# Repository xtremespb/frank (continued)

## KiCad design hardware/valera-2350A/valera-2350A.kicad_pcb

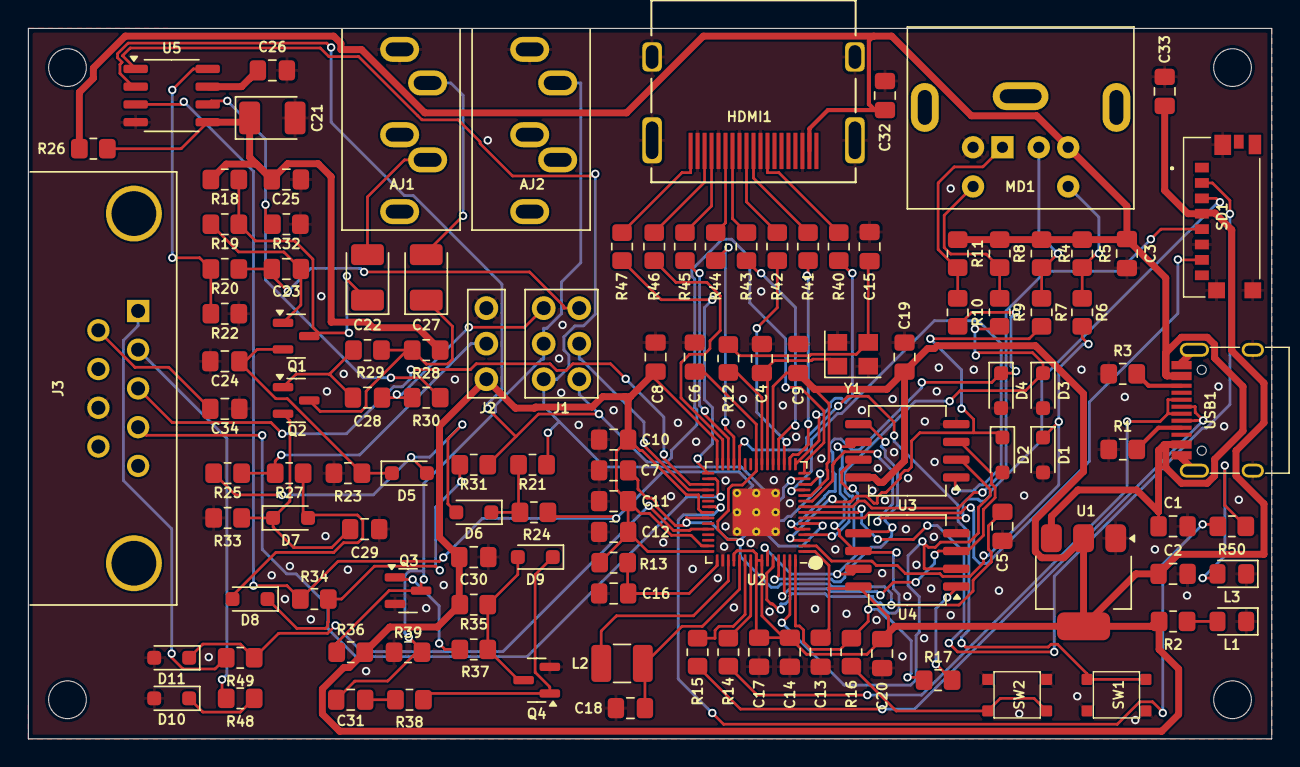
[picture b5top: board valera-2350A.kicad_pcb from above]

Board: 2 copper layers, 88.9 x 50.8 mm, 123 parts (0 on the bottom side), 92 nets.

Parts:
AJ1: Audio OUT; Jack (3.5mm)
AJ2: Audio In; Jack (3.5mm)
C1, C2, C3: 10u; Capacitor (0805)
C4, C15: 15p; Capacitor (0805)
C5, C7, C8, C9, C10, C11, C12, C13, C14, C19, C20, C24, C25, C29, C30, C31, C32, C33, C34: 100n; Capacitor (0805)
C6, C16, C17, C18: 4.7u; Capacitor (0805)
C21, C22, C27: 10u; Capacitor (3528, tantalum, polar)
C23, C26, C28: 1u; Capacitor (0805)
D1, D2, D3, D4, D10, D11: 3V3; Diode (SOD-323)
D5, D6, D7, D8, D9: 1N4148; Diode (SOD-323)
H1, H2, H3, H4: MountingHole; Mounting Hole (2.7mm)
HDMI1: HDMI Female; HDMI (female)
J1: Audio Jumpers; Pin Header (2x03)
J2: PWM Jumper; Pin Header (1x03)
J3: Gamepad; D-SUB (9 pin, male, top mount)
L1: Green; LED (0805)
L2: 3.3u; Inductor (3225)
L3: Blue; LED (0805)
MD1: Mini-DIN-6; MiniDIN (6 Pin, female)
Q1, Q2, Q3, Q4: BC850; SOT-23
R1, R3: 5.1K; Resistor (0805)
R2, R4, R5, R8, R12, R16, R18, R22, R28, R32, R36, R48, R49, R50: 1K; Resistor (0805)
R6, R7, R9, R10, R23, R39: 100R; Resistor (0805)
R11: 1k; Resistor (0805)
R13: 33R; Resistor (0805)
R14, R15: 27R; Resistor (0805)
R17: 0R; Resistor (0805)
R19, R29: 100K; Resistor (0805)
R20, R30: 20K; Resistor (0805)
R21, R31: 51R; Resistor (0805)
R24, R25, R27, R34: 200R; Resistor (0805)
R26: 10R; Resistor (0805)
R33: 100; Resistor (0805)
R35, R37, R38: 10K; Resistor (0805)
R40, R41, R42, R43, R44, R45, R46, R47: 270R; Resistor (0805)
SD1: 47571-0001; MicroSD (SMD, short)
SW1: Reset; Button (SMD, 3x3mm, 1-1)
SW2: Boot; Button (SMD, 3x3mm, 1-1)
U1: NCP1117 3.3; SOT-223
U2: RP2350A; QFN 60 (RP2350A)
U3: ESP-PSRAM32; SOIC-8
U4: W25Q128JVSQ; SOIC-8
U5: TDA1387T; SO-8
USB1: USB Type C
Y1: ABM8-272-T3; Crystal (3225)

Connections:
+3V3: C2.1, C8.1, C9.1, C10.1, C11.1, C12.1, C13.1, C14.1, C17.1, C19.1, C20.1, C30.1, C33.2, J2.3, R2.2, R13.1, R35.1, R36.1, SD1.P4 (VDD), U1.2 (VO), U2.1 (IOVDD), U2.11 (IOVDD), U2.20 (IOVDD), U2.30 (IOVDD), U2.38 (IOVDD), U2.44 (ADC_AVDD), U2.45 (IOVDD), U2.49 (VREG_VIN), U2.53 (USB_OTP_VDD), U2.54 (QSPI_IOVDD), U3.8 (VCC), U4.8 (VCC)
/Audio Out/+5VA: C21.1, C25.1, R18.1, R26.1, R28.1, U5.5 (VA)
/Audio Out/L: AJ1.T, C27.2
/Audio Out/R: AJ1.R, C22.2
/D+: R14.1, USB1.6 (DP1), USB1.8 (DP2)
/D-: R15.1, USB1.5 (DN2), USB1.7 (DN1)
/GPIO0: D1.1 (K), R6.2, U2.2 (GPIO0)
/GPIO1: D2.1 (K), R7.2, U2.3 (GPIO1)
/GPIO2: D3.1 (K), R9.2, U2.4 (GPIO2)
/GPIO3: D4.1 (K), R10.2, U2.5 (GPIO3)
/GPIO4: SD1.P7 (DAT0), U2.7 (GPIO4)
/GPIO5: SD1.P2 (CD/DAT3), U2.8 (GPIO5)
/GPIO6: SD1.P5 (CLK), U2.9 (GPIO6)
/GPIO7: SD1.P3 (CMD), U2.10 (GPIO7)
/GPIO8: U2.12 (GPIO8), U3.1 (~CE)
/GPIO9: R24.2, R34.2, U2.13 (GPIO9), U5.3 (DATA)
/GPIO10: J1.5, R21.2, U2.14 (GPIO10), U5.1 (SCLK)
/GPIO11: J1.6, R31.2, U2.15 (GPIO11), U5.2 (LRCK)
/GPIO12: R40.2, U2.16 (GPIO12)
/GPIO13: R41.2, U2.17 (GPIO13)
/GPIO14: R42.2, U2.18 (GPIO14)
/GPIO15: R43.2, U2.19 (GPIO15)
/GPIO16: R44.2, U2.27 (GPIO16)
/GPIO17: R45.2, U2.28 (GPIO17)
/GPIO18: R46.2, U2.29 (GPIO18)
/GPIO19: R47.2, U2.31 (GPIO19)
/GPIO20: J3.4, U2.32 (GPIO20)
/GPIO21: J3.3, U2.33 (GPIO21)
/GPIO22: J1.4, U2.34 (GPIO22)
/GPIO26: D10.1 (K), R48.1
/GPIO27: D11.1 (K), R49.1, U2.41 (GPIO27_ADC1)
/Gamepad/+5V: C34.1, J3.6
/Gamepad/J1_DATA: J3.2, R48.2
/Gamepad/J2_DATA: J3.1, R49.2
/LEFT_OUT: C28.1, J1.1, R30.2
/LOAD_IN_D: AJ2.T, C31.1, J1.3, Q3.3 (C), R36.2, R39.1
/PS2/PS/2 CLK: MD1.5, R8.2, R9.1
/PS2/PS/2 DATA: MD1.1, R10.1, R11.2
/PWM_EN: J2.2, R25.2, R27.1
/RIGHT_OUT: C23.1, J1.2, R20.2
/RP2350A/FLASH_SS: R17.2, U4.1 (~CS)
/RP2350A/QSPI_SCLK: U2.56 (QSPI_SCLK), U3.6 (SCLK), U4.6 (CLK)
/RP2350A/QSPI_SD0: U2.57 (QSPI_SD0), U3.5 (SI/SIO), U4.5 (DI(IO0))
/RP2350A/QSPI_SD1: U2.59 (QSPI_SD1), U3.2 (SO/SIO), U4.2 (DO(IO1))
/RP2350A/QSPI_SD2: U2.58 (QSPI_SD2), U3.3 (SIO2), U4.3 (IO2)
/RP2350A/QSPI_SD3: U2.55 (QSPI_SD3), U3.7 (SIO3), U4.7 (IO3)
/RP2350A/QSPI_SS: R16.1, R17.1, U2.60 (QSPI_SS)
/RP2350A/VREG_AVDD: C16.1, R13.2, U2.46 (VREG_AVDD)
/RP2350A/VREG_LX: L2.2, U2.48 (VREG_LX)
/RP2350A/XIN: C4.1, U2.21 (XIN), Y1.1
/RP2350A/XOUT: R12.1, U2.22 (XOUT)
/RP2350A/~USB_BOOT: R16.2, SW2.2
/RUN: SW1.1, U2.26 (RUN)
GND: AJ1.S, AJ2.S, C1.2, C2.2, C3.2, C4.2, C5.2, C6.2, C7.2, C8.2, C9.2, C10.2, C11.2, C12.2, C13.2, C14.2, C15.2, C16.2, C17.2, C18.2, C19.2, C20.2, C21.2, C24.1, C25.2, C26.2, C29.1, C30.2, C32.2, C33.1, C34.2, D1.2 (A), D2.2 (A), D3.2 (A), D4.2 (A), D10.2 (A), D11.2 (A), HDMI1.2 (G_D2), HDMI1.5 (G_D1), HDMI1.8 (G_D0), HDMI1.11 (G_CLK), HDMI1.17 (G_DDC/CEC), HDMI1.20 (SHIELD1), HDMI1.21 (SHIELD2), HDMI1.22 (SHIELD3), HDMI1.23 (SHIELD4), J2.1, J3.8, L1.1 (K), L3.1 (K), MD1.3, Q3.2 (E), Q4.2 (E), R1.1, R3.1, R22.2, R23.2, R32.2, R33.2, R39.2, SD1.G1 (GND_1), SD1.G2 (GND_2), SD1.G3 (GND_3), SD1.P6 (VSS), SW1.2, SW2.1, U1.1 (GND), U2.47 (VREG_PGND), U2.61 (GND), U3.4 (VSS), U4.4 (GND), U5.4 (AGND), USB1.1 (GND), USB1.12 (GND), USB1.13 (SHIELD), Y1.2, Y1.4
GPIO25: R50.2, U2.37 (GPIO25)
unnamed: C5.1, C6.1, C7.1, U2.6 (DVDD), U2.23 (DVDD), U2.39 (DVDD)
unnamed: C15.1, R12.2, Y1.3
unnamed: C31.2, R38.1
unnamed: D5.2 (A), D6.2 (A), R25.1
unnamed: C24.2, D5.1 (K), Q1.2 (E), R23.1
unnamed: D6.1 (K), R21.1, R24.1
unnamed: D7.2 (A), D8.2 (A), R27.2
unnamed: C29.2, D7.1 (K), Q2.2 (E), R33.1
unnamed: D8.1 (K), R31.1, R34.1
unnamed: D9.2 (A), Q4.3 (C), R35.2, R37.1
unnamed: D9.1 (K), Q4.1 (B), R38.2
unnamed: HDMI1.12 (CLKN), R40.1
unnamed: HDMI1.10 (CLKP), R41.1
unnamed: HDMI1.9 (D0N), R42.1
unnamed: HDMI1.7 (D0P), R43.1
unnamed: HDMI1.6 (D1N), R44.1
unnamed: HDMI1.4 (D1P), R45.1
unnamed: HDMI1.3 (D2N), R46.1
unnamed: HDMI1.1 (D2P), R47.1
unnamed: L1.2 (A), R2.1
unnamed: L3.2 (A), R50.1
unnamed: MD1.2, R4.2, R7.1
unnamed: MD1.6, R5.2, R6.1
unnamed: C23.2, Q1.1 (B), R19.1
unnamed: C22.1, Q1.3 (C), R18.2, R19.2
unnamed: C28.2, Q2.1 (B), R29.1
unnamed: C27.1, Q2.3 (C), R28.2, R29.2
unnamed: Q3.1 (B), R37.2
unnamed: R15.2, U2.51 (USB_DM)
unnamed: R14.2, U2.52 (USB_DP)
unnamed: C18.1, L2.1, U2.50 (VREG_FB)
unnamed: R30.1, R32.1, U5.6 (A_LEFT)
unnamed: R20.1, R22.1, U5.8 (A_RIGHT)
unnamed: C26.1, U5.7 (FLT)
unnamed: R1.2, USB1.4 (CC1)
unnamed: R3.2, USB1.10 (CC2)
VBUS: C1.1, C3.1, C32.1, HDMI1.18 (+5V), MD1.4, R4.1, R5.1, R8.1, R11.1, R26.2, U1.3 (VI), USB1.2 (VBUS), USB1.11 (VBUS)

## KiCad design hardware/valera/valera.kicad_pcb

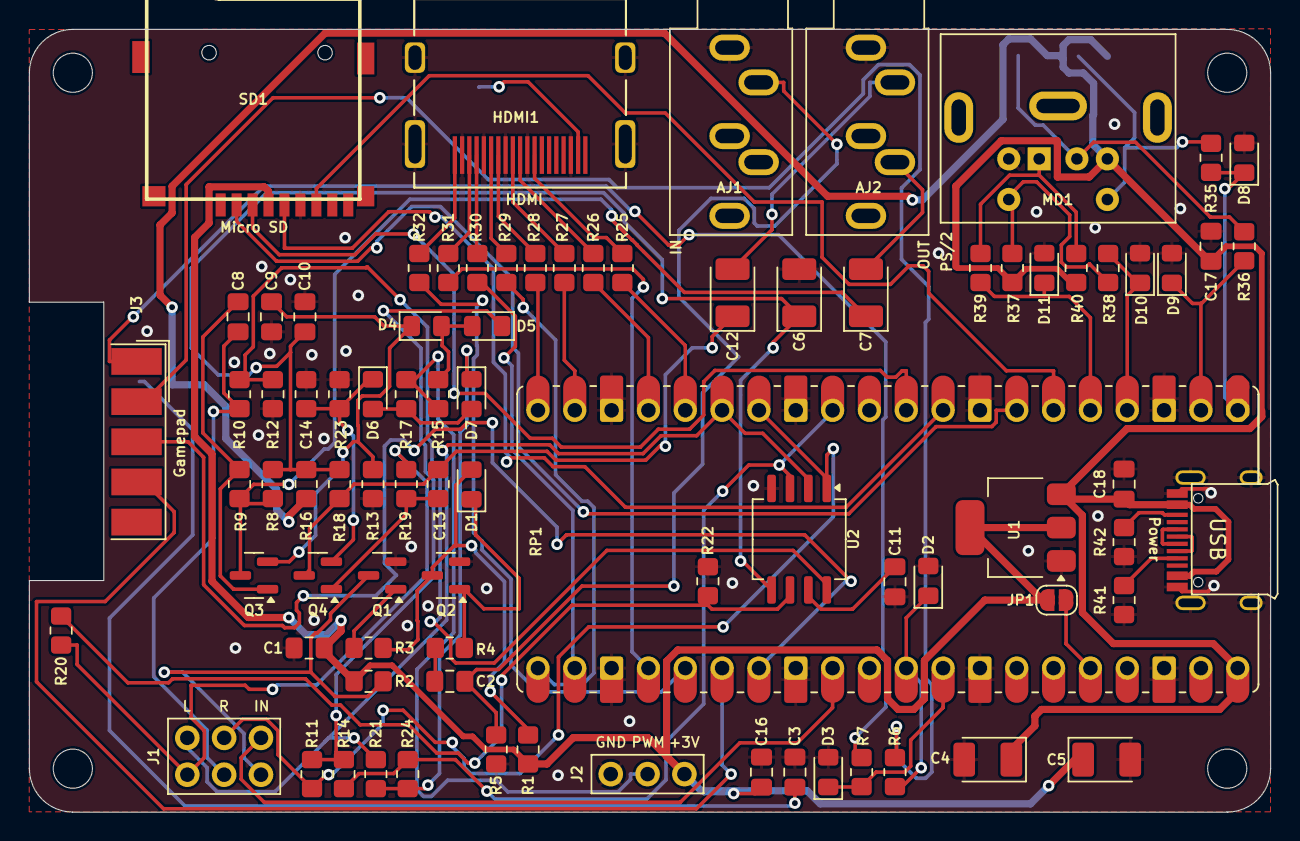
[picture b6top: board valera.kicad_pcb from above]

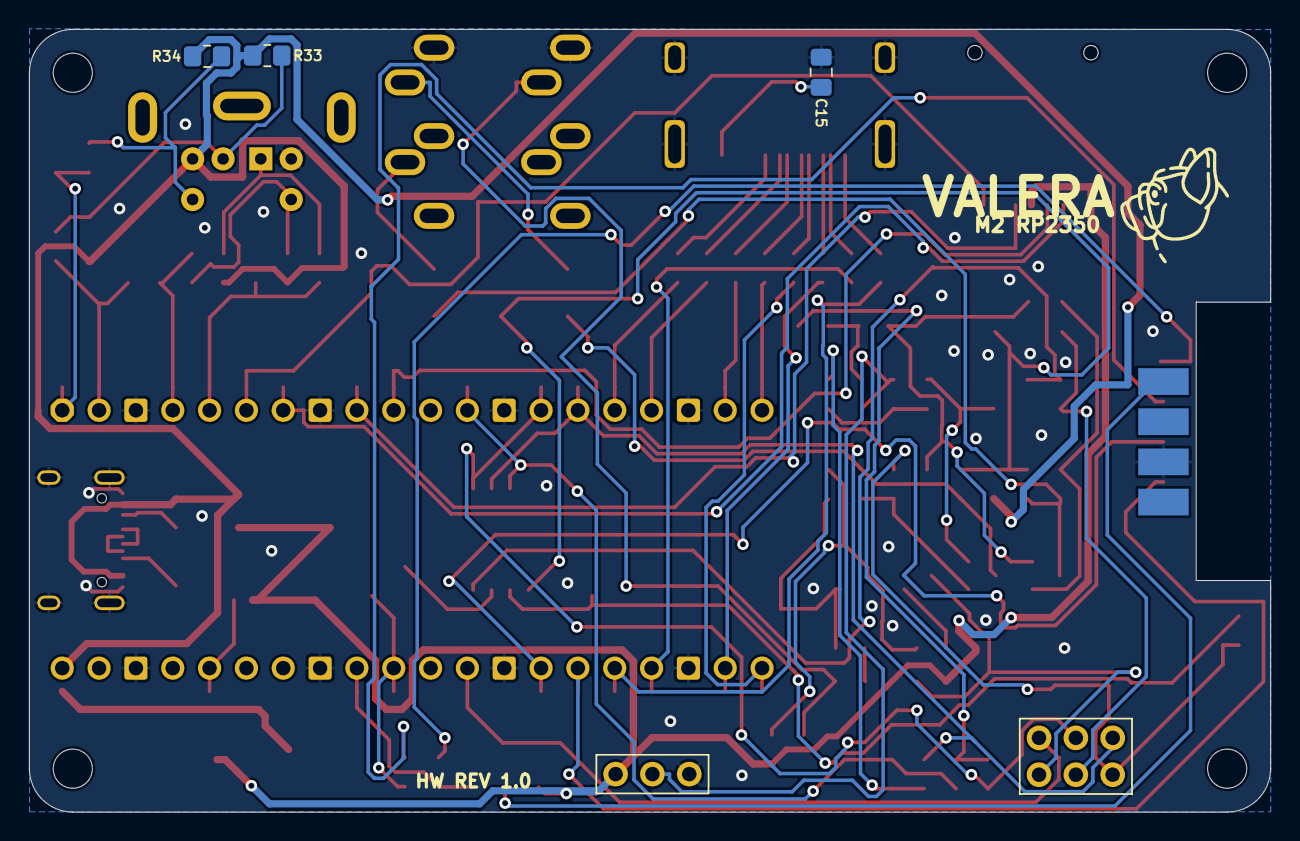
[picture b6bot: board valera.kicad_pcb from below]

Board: 2 copper layers, 85.6 x 54.0 mm, 92 parts (3 on the bottom side), 73 nets.

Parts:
AJ1: Audio IN; Jack_3.5mm
AJ2: Audio OUT; Jack_3.5mm
C1, C2, C9, C10, C15, C16: 100n; C_0805
C3: 0.1u; C_0805
C4, C5, C6, C7, C12: 10u; CT_3528
C8, C11: 1u; C_0805
C13: 1u; R_0805
C14: 100n; R_0805
C17, C18: 10u; C_0805
D1, D4, D5, D6, D7: 4148; D_0805
D2, D3, D8, D9, D10, D11: 3V3; D_0805
H1, H2, H3, H4: MountingHole; MountingHole_2.7
HDMI1: HDMI
J1: Audio Jumpers; PinHeader_2x03
J2: PWM Jumper; PinHeader_1x03
J3: JOY-1; DSUB-9_Male_EdgeMount_P2.77mm
JP1: Enable 3V3; S_Jumper
MD1: Mini-DIN-6; Connector_Mini-DIN_Female_6Pin_2rows
Q1, Q2, Q3, Q4: BC850; Q_SOT-23
R1, R3, R4: 10K; R_0805
R2, R6, R7, R8, R12, R18, R22, R33, R34, R37: 1K; R_0805
R5, R13, R35, R36, R38, R39: 100R; R_0805
R9, R19: 100K*; R_0805
R10, R20: 20K; R_0805
R11, R21: 51R; R_0805
R14, R15, R17, R24: 200R; R_0805
R16: 10R; R_0805
R23: 100; R_0805
R25, R26, R27, R28, R29, R30, R31, R32: 270R; R_0805
R40: 1k; R_0805
R41, R42: 5.1K; R_0805
RP1: Pico 2; Raspberry_Pi_Pico_SMT_THT_MOD_2
SD1: Micro_SD_Card; GCT-MEM2055-00-190-01-A
U1: AMS1117-3.3; SOT-223-3_TabPin2
U2: TDA1387T; SO_4x4
USB1: USB Type C; USB-TYPE-C-31-M-12_lib2

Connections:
+3V3: C1.1, C5.1, C16.2, J2.3, JP1.1 (A), R1.1, R2.1, SD1.4 (VDD), U1.2 (VO)
/3V3_EXT: JP1.2 (B), RP1.36 (3V3)
/AU_DATA: R14.2, R24.2, RP1.12 (GPIO9), U2.3 (DATA)
/AU_LRCK: J1.6, R21.2, RP1.15 (GPIO11), U2.2 (LRCK)
/AU_SCLK: J1.5, R11.2, RP1.14 (GPIO10), U2.1 (SCLK)
/Audio Out/+5VA: C6.1, C10.1, R8.1, R16.1, R18.1, U2.5 (VA)
/Audio Out/L: AJ2.T, C12.2
/Audio Out/R: AJ2.R, C7.2
/CLKN: R25.2, RP1.16 (GPIO12)
/CLKP: R26.2, RP1.17 (GPIO13)
/D0N: R27.2, RP1.19 (GPIO14)
/D0P: R28.2, RP1.20 (GPIO15)
/D1N: R29.2, RP1.21 (GPIO16)
/D1P: R30.2, RP1.22 (GPIO17)
/D2N: R31.2, RP1.24 (GPIO18)
/D2P: R32.2, RP1.25 (GPIO19)
/Gamepad/+5V: C3.1, J3.6
/Gamepad/J1_DATA: J3.2, R6.2
/Gamepad/J2_DATA: J3.1, R7.2
/HDMI/+5V: C15.1, HDMI1.18 (+5V)
/JOY_PIN1: D3.1 (K), R7.1, RP1.32 (GPIO27_ADC1)
/JOY_PIN2: D2.1 (K), R6.1, RP1.31 (GPIO26_ADC0)
/JOY_PIN3: J3.3, RP1.27 (GPIO21)
/JOY_PIN4: J3.4, RP1.26 (GPIO20)
/KB_CLK_3V: D10.1 (K), R38.2, RP1.4 (GPIO2)
/KB_DATA_3V: D11.1 (K), R39.2, RP1.5 (GPIO3)
/LEFT_OUT: C13.1, J1.1, R20.2
/LOAD_IN: J1.4, RP1.29 (GPIO22)
/LOAD_IN_D: J1.3, Q1.3 (C), R2.2
/MS_CLK_3V: D8.1 (K), R35.2, RP1.1 (GPIO0)
/MS_DATA_3V: D9.1 (K), R36.2, RP1.2 (GPIO1)
/PS2/PS/2 CLK: MD1.5, R37.2, R38.1
/PS2/PS/2 DATA: MD1.1, R39.1, R40.2
/PWM_EN: J2.2, R15.2, R17.1
/Power/D+: USB1.6 (DP1), USB1.8 (DP2)
/Power/D-: USB1.5 (DN2), USB1.7 (DN1)
/RIGHT_OUT: C8.1, J1.2, R10.2
/SD_CLK: RP1.9 (GPIO6), SD1.5 (CLK)
/SD_CS: RP1.7 (GPIO5), SD1.2 (DAT3/CD)
/SD_MISO: RP1.6 (GPIO4), SD1.7 (DAT0)
/SD_MOSI: RP1.10 (GPIO7), SD1.3 (CMD)
/Tape Loader/LOAD_IN: AJ1.T, C2.1, R5.1
GND: AJ1.S, AJ2.S, C1.2, C3.2, C4.2, C5.2, C6.2, C9.1, C10.2, C11.2, C14.1, C15.2, C16.1, C17.2, C18.2, D2.2 (A), D3.2 (A), D8.2 (A), D9.2 (A), D10.2 (A), D11.2 (A), HDMI1.2 (G_D2), HDMI1.5 (G_D1), HDMI1.8 (G_D0), HDMI1.11 (G_CLK), HDMI1.17 (G_DDC/CEC), HDMI1.20 (SHIELD1), HDMI1.21 (SHIELD2), HDMI1.22 (SHIELD3), HDMI1.23 (SHIELD4), J2.1, J3.8, MD1.3, Q1.2 (E), Q2.2 (E), R5.2, R12.2, R13.2, R22.2, R23.2, R41.1, R42.1, RP1.3 (GND), RP1.8 (GND), RP1.13 (GND), RP1.18 (GND), RP1.23 (GND), RP1.28 (GND), RP1.33 (AGND), RP1.38 (GND), SD1.6 (VSS), U1.1 (GND), U2.4 (AGND), USB1.1 (GND), USB1.12 (GND), USB1.13 (SHIELD)
unnamed: C2.2, R4.1
unnamed: D1.2 (A), Q2.3 (C), R1.2, R3.1
unnamed: D1.1 (K), Q2.1 (B), R4.2
unnamed: D4.2 (A), D5.2 (A), R15.1
unnamed: C9.2, D4.1 (K), Q3.2 (E), R13.1
unnamed: D5.1 (K), R11.1, R14.1
unnamed: D6.2 (A), D7.2 (A), R17.2
unnamed: C14.2, D6.1 (K), Q4.2 (E), R23.1
unnamed: D7.1 (K), R21.1, R24.1
unnamed: HDMI1.12 (CLKN), R25.1
unnamed: HDMI1.10 (CLKP), R26.1
unnamed: HDMI1.9 (D0N), R27.1
unnamed: HDMI1.7 (D0P), R28.1
unnamed: HDMI1.6 (D1N), R29.1
unnamed: HDMI1.4 (D1P), R30.1
unnamed: HDMI1.3 (D2N), R31.1
unnamed: HDMI1.1 (D2P), R32.1
unnamed: MD1.2, R33.2, R36.1
unnamed: MD1.6, R34.2, R35.1
unnamed: Q1.1 (B), R3.2
unnamed: C8.2, Q3.1 (B), R9.1
unnamed: C7.1, Q3.3 (C), R8.2, R9.2
unnamed: C13.2, Q4.1 (B), R19.1
unnamed: C12.1, Q4.3 (C), R18.2, R19.2
unnamed: R20.1, R22.1, U2.6 (A_LEFT)
unnamed: R10.1, R12.1, U2.8 (A_RIGHT)
unnamed: C11.1, U2.7 (FLT)
unnamed: R41.2, USB1.4 (CC1)
unnamed: R42.2, USB1.10 (CC2)
VBUS: C4.1, C17.1, C18.1, MD1.4, R16.2, R33.1, R34.1, R37.1, R40.1, RP1.40 (VBUS), U1.3 (VI), USB1.2 (VBUS), USB1.11 (VBUS)

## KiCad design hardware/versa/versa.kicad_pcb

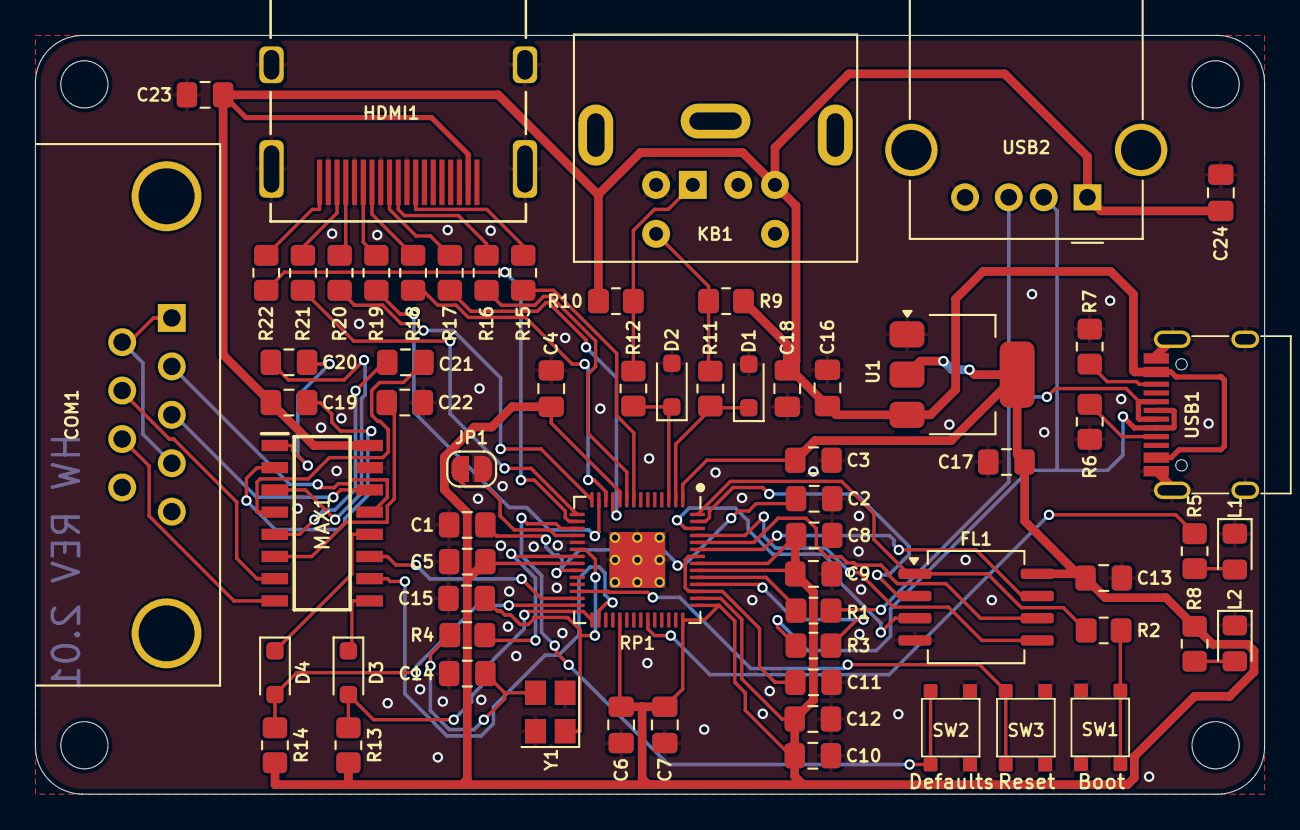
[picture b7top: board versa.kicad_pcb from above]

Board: 2 copper layers, 70.3 x 43.4 mm, 70 parts (0 on the bottom side), 63 nets.

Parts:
C1, C2, C3, C4, C5, C6, C7, C8, C9, C10, C13, C18, C23: 100n; Capacitor (0805)
C11, C12, C19, C20, C21, C22: 1u; Capacitor (0805)
C14, C15: 15p; Capacitor (0805)
C16, C17, C24: 10u; Capacitor (0805)
COM1: D-SUB 9 Male; D-SUB (9 pin, male, top mount)
D1, D2: 3V3; Diode (SOD-323)
D3, D4: 1N4148; Diode (SOD-323)
FL1: W25Q128JVSIQ; SOIC-8
H1, H2, H3, H4: MountingHole; MountingHole_2.7mm
HDMI1: DC3RX19JA2; HDMI (female)
JP1: HDMI_DEF; Jumper (solder)
KB1: PS/2; MiniDIN (6 Pin, female)
L1: Blue; LED (0805)
L2: Green; LED (0805)
MAX1: MAX232CSE+; SOIC127P600X175-16N
R1, R3: 27R; Resistor (0805)
R2, R4, R5, R8, R9, R13, R14: 1K; Resistor (0805)
R6, R7: 5.1K; Resistor (0805)
R10: 1k; Resistor (0805)
R11, R12: 100R; Resistor (0805)
R15, R16, R17, R18, R19, R20, R21, R22: 270R; Resistor (0805)
RP1: RP2040; QFN 56
SW1: Flash Button; Button (SMD, 3x3mm)
SW2, SW3: KLS7-TS3302; Button (SMD, 3x3mm)
U1: NCP1117 3.3; SOT-223
USB1: USB4215; USB Type C
USB2: 676430910; USB Type A (single)
Y1: 12 MHz; Crystal (3225)

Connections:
+3V3: C3.1, C4.1, C5.1, C6.1, C7.1, C8.1, C9.1, C10.1, C12.1, C13.1, C17.1, FL1.8 (VCC), R8.2, R13.2, R14.2, RP1.1 (IOVDD), RP1.10 (IOVDD), RP1.22 (IOVDD), RP1.33 (IOVDD), RP1.42 (IOVDD), RP1.43 (ADC_AVDD), RP1.44 (VREG_IN), RP1.48 (USB_VDD), RP1.49 (IOVDD), U1.2 (VO)
/D+: R1.1, USB1.6 (DP1), USB1.8 (DP2), USB2.3 (D+)
/D-: R3.1, USB1.5 (DN2), USB1.7 (DN1), USB2.2 (D-)
/GPIO0: D1.1 (K), R11.2, RP1.2 (GPIO0)
/GPIO1: D2.1 (K), R12.2, RP1.3 (GPIO1)
/GPIO6: R15.2, RP1.8 (GPIO6)
/GPIO7: R16.2, RP1.9 (GPIO7)
/GPIO8: R17.2, RP1.11 (GPIO8)
/GPIO9: R18.2, RP1.12 (GPIO9)
/GPIO10: R19.2, RP1.13 (GPIO10)
/GPIO11: R20.2, RP1.14 (GPIO11)
/GPIO12: R21.2, RP1.15 (GPIO12)
/GPIO13: R22.2, RP1.16 (GPIO13)
/GPIO14: RP1.17 (GPIO14), SW2.3, SW2.4
/GPIO15: JP1.1 (A), RP1.18 (GPIO15)
/GPIO16: MAX1.11 (T1IN), RP1.27 (GPIO16)
/GPIO17: D4.2 (A), R14.1, RP1.28 (GPIO17)
/GPIO18: D3.2 (A), R13.1, RP1.29 (GPIO18)
/GPIO19: MAX1.10 (T2IN), RP1.30 (GPIO19)
/RP2040/GPIO25: R5.2, RP1.37 (GPIO25)
/RP2040/QSPI_SCLK: FL1.6 (CLK), RP1.52 (QSPI_SCLK)
/RP2040/QSPI_SD0: FL1.5 (DI(IO0)), RP1.53 (QSPI_SD0)
/RP2040/QSPI_SD1: FL1.2 (DO(IO1)), RP1.55 (QSPI_SD1)
/RP2040/QSPI_SD2: FL1.3 (IO2), RP1.54 (QSPI_SD2)
/RP2040/QSPI_SD3: FL1.7 (IO3), RP1.51 (QSPI_SD3)
/RP2040/QSPI_SS: FL1.1 (~CS), R2.1, RP1.56 (QSPI_SS)
/RP2040/XIN: C15.1, RP1.20 (XIN), Y1.1
/RP2040/XOUT: R4.1, RP1.21 (XOUT)
/RP2040/~USB_BOOT: R2.2, SW1.3, SW1.4
/RS232/C1+: C20.2, MAX1.1 (C1+)
/RS232/C1-: C20.1, MAX1.3 (C1-)
/RS232/C2+: C21.2, MAX1.4 (C2+)
/RS232/C2-: C21.1, MAX1.5 (C2-)
/RS232/CTS_IN: COM1.7, MAX1.7 (T2OUT)
/RS232/CTS_MAX: D3.1 (K), MAX1.9 (R2OUT)
/RS232/RTS_IN: COM1.8, MAX1.8 (R2IN)
/RS232/RX_IN: COM1.3, MAX1.14 (T1OUT)
/RS232/RX_MAX: D4.1 (K), MAX1.12 (R1OUT)
/RS232/TX_IN: COM1.2, MAX1.13 (R1IN)
/RS232/V+: C19.1, MAX1.2 (V+)
/RS232/V-: C22.1, MAX1.6 (V-)
/RUN: RP1.26 (RUN), SW3.3, SW3.4
GND: C1.2, C2.2, C3.2, C4.2, C5.2, C6.2, C7.2, C8.2, C9.2, C10.2, C11.2, C12.2, C13.2, C14.2, C15.2, C16.2, C17.2, C18.2, C22.2, C23.2, C24.1, COM1.5, D1.2 (A), D2.2 (A), FL1.4 (GND), HDMI1.2 (G_D2), HDMI1.5 (G_D1), HDMI1.8 (G_D0), HDMI1.11 (G_CLK), HDMI1.17 (G_DDC/CEC), HDMI1.20 (SHIELD1), HDMI1.21 (SHIELD2), HDMI1.22 (SHIELD3), HDMI1.23 (SHIELD4), JP1.2 (B), KB1.3, L1.1 (K), L2.1 (K), MAX1.15 (GND), R6.1, R7.1, RP1.19 (TESTEN), RP1.57 (GND), SW1.1, SW1.2, SW2.1, SW2.2, SW3.1, SW3.2, U1.1 (GND), USB1.1 (GND), USB1.12 (GND), USB1.13 (SHIELD), USB2.4 (GND), USB2.5 (Shield), Y1.2, Y1.4
unnamed: C14.1, R4.2, Y1.3
unnamed: COM1.1, COM1.4, COM1.6
unnamed: HDMI1.12 (CLKN), R15.1
unnamed: HDMI1.10 (CLKP), R16.1
unnamed: HDMI1.9 (D0N), R17.1
unnamed: HDMI1.7 (D0P), R18.1
unnamed: HDMI1.6 (D1N), R19.1
unnamed: HDMI1.4 (D1P), R20.1
unnamed: HDMI1.3 (D2N), R21.1
unnamed: HDMI1.1 (D2P), R22.1
unnamed: KB1.1, R10.2, R12.1
unnamed: KB1.5, R9.2, R11.1
unnamed: L1.2 (A), R5.1
unnamed: L2.2 (A), R8.1
unnamed: R3.2, RP1.46 (USB_DM)
unnamed: R1.2, RP1.47 (USB_DP)
unnamed: C1.1, C2.1, C11.1, RP1.23 (DVDD), RP1.45 (VREG_VOUT), RP1.50 (DVDD)
unnamed: R6.2, USB1.4 (CC1)
unnamed: R7.2, USB1.10 (CC2)
VBUS: C16.1, C18.1, C19.2, C23.1, C24.2, HDMI1.18 (+5V), KB1.4, MAX1.16 (VCC), R9.1, R10.1, U1.3 (VI), USB1.2 (VBUS), USB1.11 (VBUS), USB2.1 (VBUS)
